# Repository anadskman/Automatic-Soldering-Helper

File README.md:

# Automatic Soldering Helper

A small robot arm that can help hold wires, PCBs and other parts while I'm soldering.

I wanted to make something like a motorised helping hand that I can move around with buttons instead of having to keep adjusting normal helping hands every time.

I already had most of the motors and electronics so I decided to try make the arm mostly out of parts I already had.

## How It Works

The whole arm rotates around the base using a **28BYJ-48 stepper motor** and a **ULN2003 driver**.

The rest of the arm uses 4 small 9g servos:

- Shoulder
- Elbow
- Wrist
- Clamp

I originally planned on using a gear ratio for the base because I thought the stepper might struggle with the weight of the arm.

After printing most of the arm and seeing how light it actually was I decided to remove the whole gear ratio part and just attach the motor directly to the arm. This also makes the base way simpler and smaller.

## Testing

Before buying the final electronics I printed everything for the arm except the final motor base and connected it to an Arduino Uno just to confirm the idea would actually work.

I only have 3 potentiometers so for testing I used them to control the servos and switched between the wrist and clamp when needed.

Kinda surprisingly it worked pretty well.

There is a small bit of electrical noise making the servos vibrate but I'm adding a 1000uF capacitor to the final electronics which should help with that.

The Arduino is only being used for testing. The final version will use an ESP32.

## Clamp

I printed a small basic clamp for the first test just to make sure the servo could actually open and close something.

After that I redesigned it into a bigger clamp taking inspiration from some videos I saw on Instagram.

The bigger one should be much more useful for actually holding wires, connectors and small PCBs so I think I'll use that for the final version.

The clamp is controlled by another 9g servo.

## Controls

I wanted the final arm to use physical controls instead of needing a computer every time I want to move it.

I'm using:

- 3 potentiometers
- 6 momentary buttons

The potentiometers can be used to manually position the shoulder, elbow and wrist.

The buttons can then be used for things like:

- Saved positions
- Moving the base
- Opening and closing the clamp
- Home
- Changing modes

The ESP32 can save arm positions so I can move the arm somewhere useful and then return to that position later without manually adjusting everything again.

## Saved Positions

A saved position can store:

- Base position
- Shoulder angle
- Elbow angle
- Wrist angle
- Clamp position

This means I could have different positions for stuff like holding wires or holding a PCB.

The positions will be stored on the ESP32 so they don't disappear every time it loses power.

## Base

The base uses the 28BYJ-48 stepper motor I already had.

I originally designed a larger base with printed gears to increase the torque but after actually printing the arm it was much lighter than I expected.

Because of that I decided to remove the gears and just drive the rotating part directly from the stepper.

There will also be a limit switch so the arm can find its home position when it starts.

## Table Mount

For attaching the whole thing to my desk I'm going to reuse the clamp from my old helping hands.

It already works well for attaching stuff to the edge of a table so there isn't much point designing another clamp.

The helping hands clamp will just slot into a mount on the bottom of the arm.

## Electronics

The final controller will be an **ESP32 CH340C USB-C development board**.

The servos aren't going to be powered directly from the ESP32.

They will use the 5V power rail and all of the grounds will be connected together.

I'm also adding a 1000uF capacitor across the servo power to help with the small amount of electrical noise I noticed while testing.

The stepper motor will be controlled through its ULN2003 board.

## PCB

I don't really need a normal manufactured PCB for this project so I'm making a 3D printed one instead.

The PCB will basically have slots and paths where I can insert the wires to keep everything organised.

I redesigned the PCB after working out the final electronics and made sure to export the traces in the STEP this time because I forgot to last time and ended up drawing them by hand in Fusion.

The ESP32 and other electronics can then mount onto this inside the case.

## Firmware

The final firmware will run on the ESP32.

Instead of using GRBL I decided to make the position system specifically for the arm since only the base uses a stepper and everything else uses servos.

The firmware will handle:

- Manual movement
- Servo control
- Stepper control
- Clamp control
- Saved positions
- Base homing
- Smooth movement
- Physical buttons
- Potentiometer controls

This should make it pretty easy to use while I'm actually soldering instead of having to control it from my computer.

## BOM

| Item | Qty | Status | Price | Notes |
| --- | ---: | --- | ---: | --- |
| [ESP32-CH340C-Type-C](https://www.aliexpress.com/item/1005008723399881.html) | 1 | Buy | $5.03 | Main controller |
| [1000uF 50V Electrolytic Capacitors](https://www.aliexpress.com/item/1005005920255833.html) | 5 | Buy | $2.22 | Servo power smoothing |
| [M2 Hex Socket Button Head Screw Kit](https://www.aliexpress.com/item/1005007278965396.html) | 1 | Buy | $6.99 | Arm assembly |
| [DS228/DS428 12mm Green Momentary Pushbuttons](https://www.aliexpress.com/item/1005008558481882.html) | 6 | Buy | $3.25 | Physical controls |
| 28BYJ-48 5V Stepper Motor | 1 | Owned | $0.00 | Rotates the arm |
| ULN2003 Stepper Driver Board | 1 | Owned | $0.00 | Drives the stepper |
| 9g Servo | 4 | Owned | $0.00 | Shoulder, elbow, wrist and clamp |
| 10k Potentiometer | 3 | Owned | $0.00 | Manual arm controls |
| Limit Switch | 1 | Owned | $0.00 | Base homing |
| 10k Resistor | 1 | Owned | $0.00 | Limit switch pull-up |

### Order Cost

| | Cost |
| --- | ---: |
| Subtotal | $17.56 |
| Savings | -$0.19 |
| Shipping | $0.00 |
| Estimated import charges | $16.93 |
| **Total** | **$34.30** |

## Current Progress

So far I've:

- Designed the arm in CAD
- Printed most of the arm
- Designed the clamp
- Tested the servos with an Arduino Uno
- Confirmed the arm can actually move
- Simplified the rotating base
- Planned the ESP32 controls
- Planned the saved position system
- Designed the 3D printed PCB
- Worked out the final BOM

The main thing now is getting the final parts and putting everything together properly.

## Images

| Schematic | PCB | Case |
| --- | --- | --- |
|  |  |  |

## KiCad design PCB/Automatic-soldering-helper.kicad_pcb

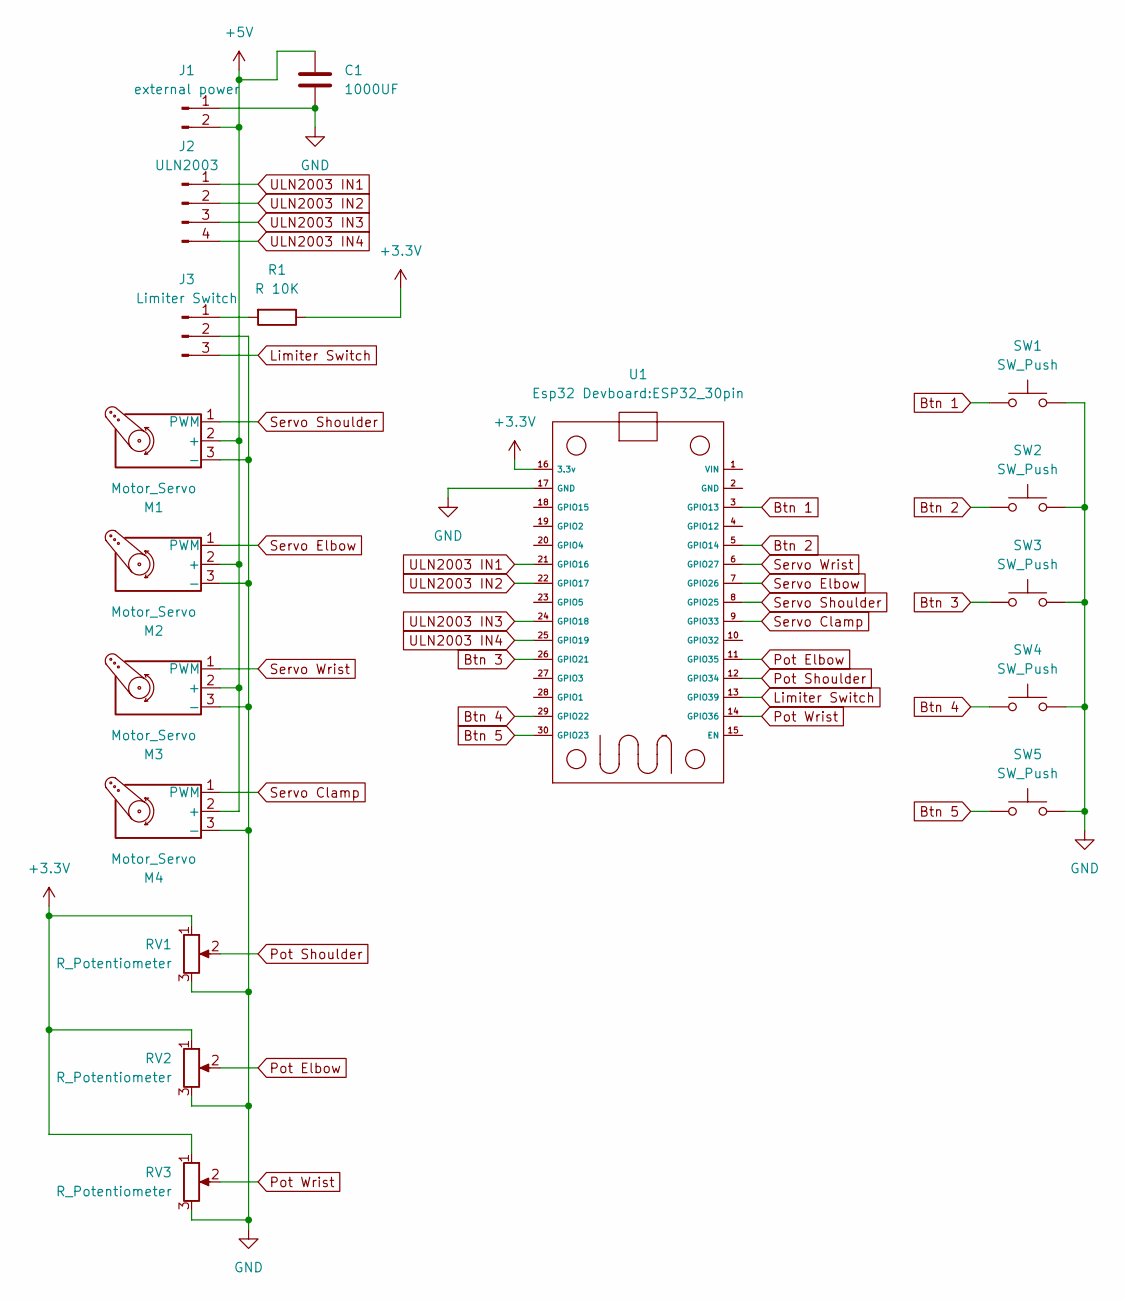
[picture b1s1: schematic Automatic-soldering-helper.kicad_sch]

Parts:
C1: 1000UF; CP_Radial_D6.3mm_P2.50mm
J1: external power; PinSocket_1x02_P2.54mm_Vertical
J2: ULN2003; PinSocket_1x04_P2.54mm_Vertical
J3: Limiter Switch; PinSocket_1x03_P2.54mm_Vertical
M1, M2, M3, M4: Motor_Servo; PinHeader_1x03_P2.54mm_Vertical
R1: R 10K; R_Axial_DIN0204_L3.6mm_D1.6mm_P7.62mm_Horizontal
RV1, RV2, RV3: R_Potentiometer; PinSocket_1x03_P2.54mm_Vertical
SW1, SW2, SW3, SW4, SW5: SW_Push; PinSocket_1x02_P2.54mm_Vertical
U1: ESP32_30pin

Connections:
+3.3V: R1.1, RV1.1, RV2.1, RV3.1, U1.16 (3.3v)
+5V: C1.2, J1.2, M1.2 (+), M2.2 (+), M3.2 (+), M4.2 (+)
Btn 1: SW1.1, U1.3 (GPIO13)
Btn 2: SW2.1, U1.5 (GPIO14)
Btn 3: SW3.1, U1.26 (GPIO21)
Btn 4: SW4.1, U1.29 (GPIO22)
Btn 5: SW5.1, U1.30 (GPIO23)
GND: C1.1, J1.1, J3.2, M1.3 (-), M2.3 (-), M3.3 (-), M4.3 (-), RV1.3, RV2.3, RV3.3, SW1.2, SW2.2, SW3.2, SW4.2, SW5.2, U1.17 (GND)
Limiter Switch: J3.3, U1.13 (GPIO39)
unnamed: J3.1, R1.2
Pot Elbow: RV2.2, U1.11 (GPIO35)
Pot Shoulder: RV1.2, U1.12 (GPIO34)
Pot Wrist: RV3.2, U1.14 (GPIO36)
Servo Clamp: M4.1 (PWM), U1.9 (GPIO33)
Servo Elbow: M2.1 (PWM), U1.7 (GPIO26)
Servo Shoulder: M1.1 (PWM), U1.8 (GPIO25)
Servo Wrist: M3.1 (PWM), U1.6 (GPIO27)
ULN2003 IN1: J2.1, U1.21 (GPIO16)
ULN2003 IN2: J2.2, U1.22 (GPIO17)
ULN2003 IN3: J2.3, U1.24 (GPIO18)
ULN2003 IN4: J2.4, U1.25 (GPIO19)

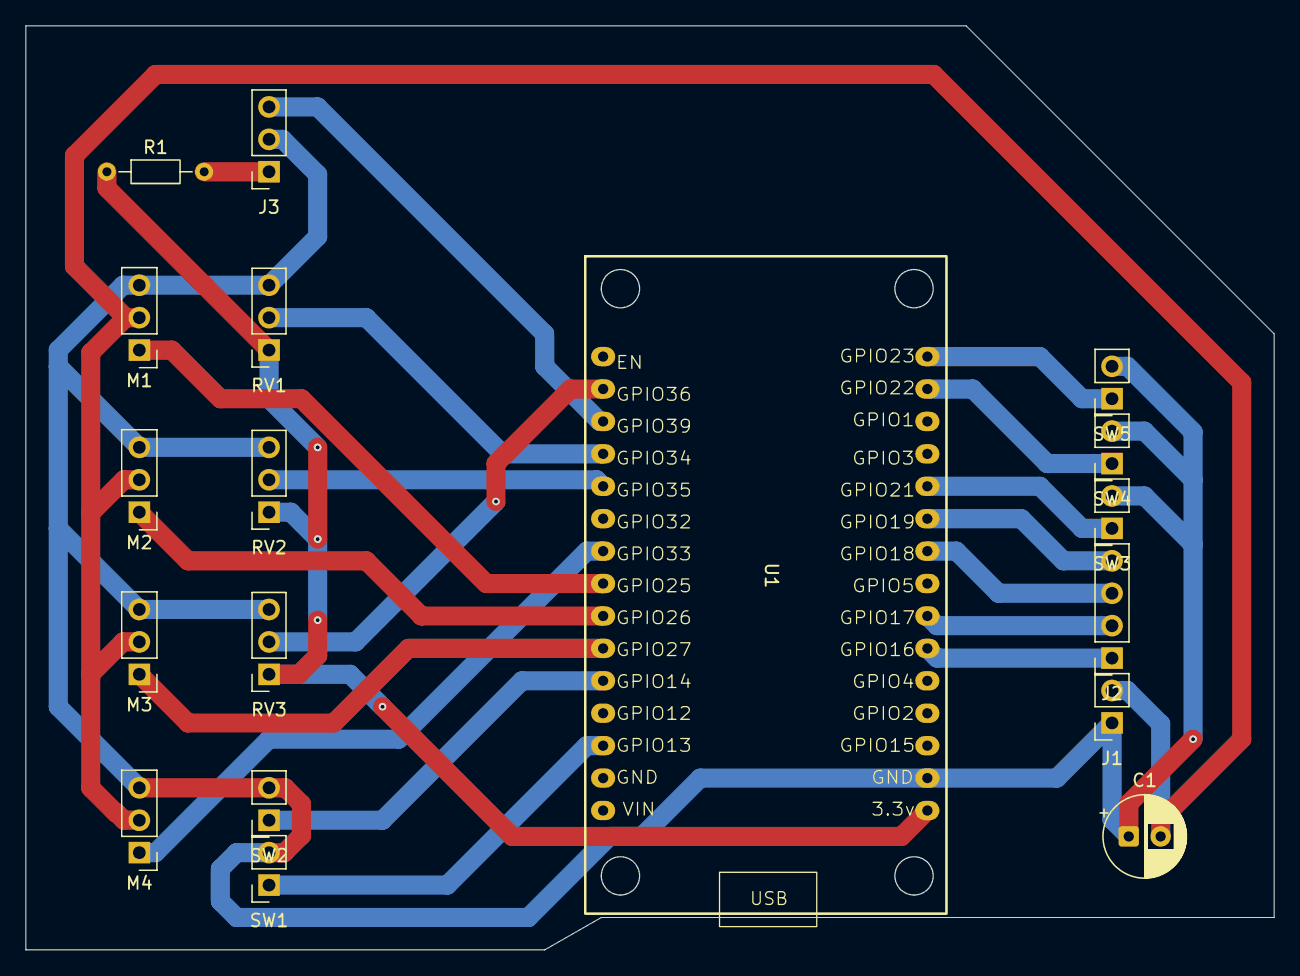
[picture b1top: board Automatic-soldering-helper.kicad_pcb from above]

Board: 2 copper layers, 97.8 x 72.4 mm, 18 parts (0 on the bottom side), 21 nets.
